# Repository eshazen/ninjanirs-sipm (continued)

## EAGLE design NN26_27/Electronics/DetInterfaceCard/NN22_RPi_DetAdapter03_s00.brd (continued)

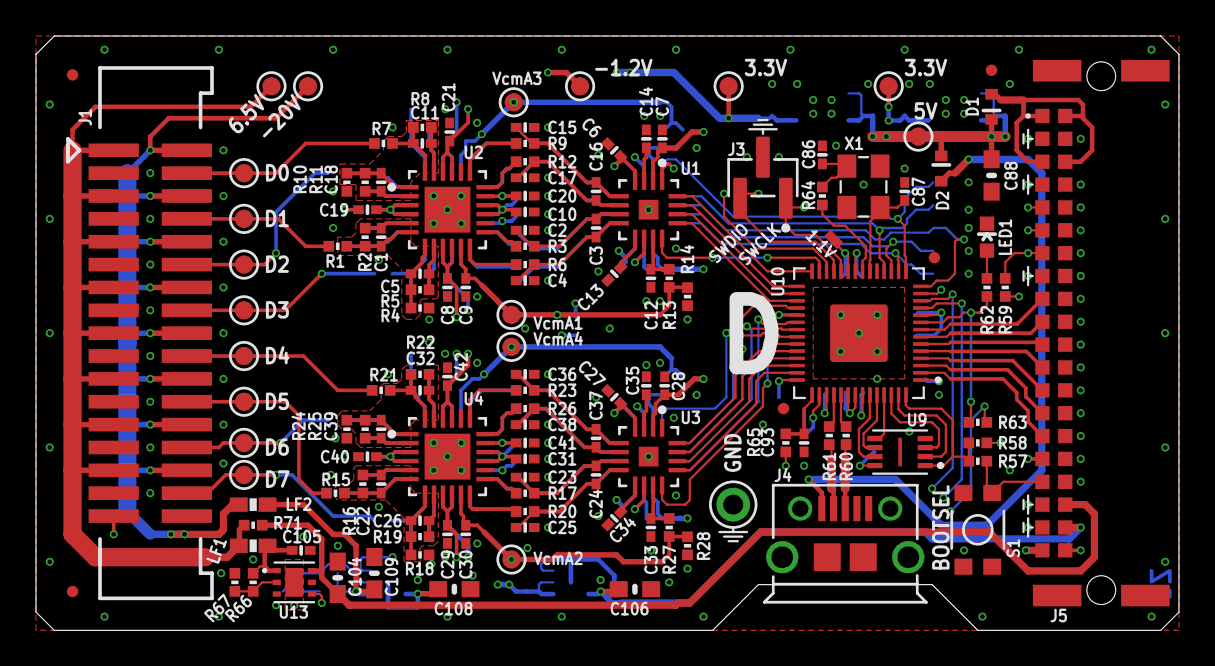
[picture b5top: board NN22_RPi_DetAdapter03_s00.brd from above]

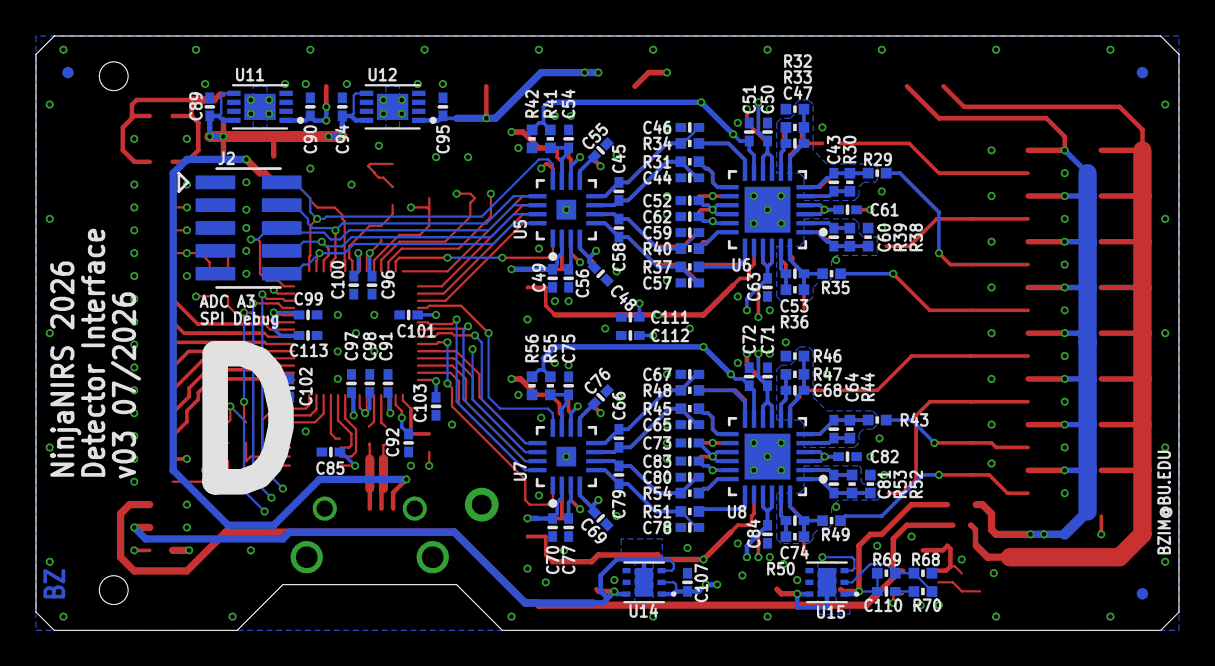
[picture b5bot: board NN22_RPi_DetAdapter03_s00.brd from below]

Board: 6 copper layers, 63.5 x 33.0 mm, 239 parts (105 on the bottom side), 156 nets.

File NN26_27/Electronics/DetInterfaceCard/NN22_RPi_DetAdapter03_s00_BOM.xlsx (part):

Designator | Value | Footprint | Populate | MPN | Manufacturer
C1 | 330p | 0402-CAP | 1 | GRM1555C1H331JA01D | Murata
C10 | 0.1u | 0402-CAP | 1 | GRM155R71H104KE14D | Murata
C100 | 0.1u | 0402-CAP | 1 | GRM155R71H104KE14D | Murata
C101 | 0.1u | 0402-CAP | 1 | GRM155R71H104KE14D | Murata
C102 | 0.1u | 0402-CAP | 1 | GRM155R71H104KE14D | Murata
C103 | 0.1u | 0402-CAP | 1 | GRM155R71H104KE14D | Murata
C104 | 10u | 0603-CAP | 1 | GRM188R6YA106MA73D | Murata
C105 | 4.7u | 0402-CAP | 1 | CL05A475MP5NRNC | Samsung
C106 | 10u | 0603-CAP | 1 | GRM188R6YA106MA73D | Murata
C107 | 4.7u | 0402-CAP | 1 | CL05A475MP5NRNC | Samsung
C108 | 10u | 0603-CAP | 1 | GRM188R6YA106MA73D | Murata
C109 | 10u | 0603-CAP | 1 | GRM188R6YA106MA73D | Murata
C11 | 330p | 0402-CAP | 1 | GRM1555C1H331JA01D | Murata
C110 | 33n | 0402-CAP | 1 | GCM155R71E333KA55D | Murata
C111 | 4.7u | 0402-CAP | 1 | CL05A475MP5NRNC | Samsung
C112 | 4.7u | 0402-CAP | 1 | CL05A475MP5NRNC | Samsung
C113 | 4.7u | 0402-CAP | 1 | CL05A475MP5NRNC | Samsung
C12 | 1u | 0402-CAP | 1 | CL05A105KP5NNNC | Samsung
C13 | 0.1u | 0402-CAP | 1 | GRM155R71H104KE14D | Murata
C14 | 1u | 0402-CAP | 1 | CL05A105KP5NNNC | Samsung
C15 | 1n | 0402-CAP | 1 | GRM1555C1H102JA01D | Murata
C16 | 1n | 0402-CAP | 1 | GRM1555C1H102JA01D | Murata
C17 | 1n | 0402-CAP | 1 | GRM1555C1H102JA01D | Murata
C18 | 330p | 0402-CAP | 1 | GRM1555C1H331JA01D | Murata
C19 | 0.1u | 0402-CAP | 1 | GRM155R71H104KE14D | Murata
C2 | 1n | 0402-CAP | 1 | GRM1555C1H102JA01D | Murata
C20 | 0.1u | 0402-CAP | 1 | GRM155R71H104KE14D | Murata
C21 | 0.1u | 0402-CAP | 1 | GRM155R71H104KE14D | Murata
C22 | 330p | 0402-CAP | 1 | GRM1555C1H331JA01D | Murata
C23 | 1n | 0402-CAP | 1 | GRM1555C1H102JA01D | Murata
C24 | 1n | 0402-CAP | 1 | GRM1555C1H102JA01D | Murata
C25 | 1n | 0402-CAP | 1 | GRM1555C1H102JA01D | Murata
C26 | 330p | 0402-CAP | 1 | GRM1555C1H331JA01D | Murata
C27 | 1u | 0402-CAP | 1 | CL05A105KP5NNNC | Samsung
C28 | 1u | 0402-CAP | 1 | CL05A105KP5NNNC | Samsung
C29 | 0.1u | 0402-CAP | 1 | GRM155R71H104KE14D | Murata
C3 | 1n | 0402-CAP | 1 | GRM1555C1H102JA01D | Murata
C30 | 0.1u | 0402-CAP | 1 | GRM155R71H104KE14D | Murata
C31 | 0.1u | 0402-CAP | 1 | GRM155R71H104KE14D | Murata
C32 | 330p | 0402-CAP | 1 | GRM1555C1H331JA01D | Murata
C33 | 1u | 0402-CAP | 1 | CL05A105KP5NNNC | Samsung
C34 | 0.1u | 0402-CAP | 1 | GRM155R71H104KE14D | Murata
C35 | 1u | 0402-CAP | 1 | CL05A105KP5NNNC | Samsung
C36 | 1n | 0402-CAP | 1 | GRM1555C1H102JA01D | Murata
C37 | 1n | 0402-CAP | 1 | GRM1555C1H102JA01D | Murata
C38 | 1n | 0402-CAP | 1 | GRM1555C1H102JA01D | Murata
C39 | 330p | 0402-CAP | 1 | GRM1555C1H331JA01D | Murata
C4 | 1n | 0402-CAP | 1 | GRM1555C1H102JA01D | Murata
C40 | 0.1u | 0402-CAP | 1 | GRM155R71H104KE14D | Murata
C41 | 0.1u | 0402-CAP | 1 | GRM155R71H104KE14D | Murata
C42 | 0.1u | 0402-CAP | 1 | GRM155R71H104KE14D | Murata
C43 | 330p | 0402-CAP | 1 | GRM1555C1H331JA01D | Murata
C44 | 1n | 0402-CAP | 1 | GRM1555C1H102JA01D | Murata
C45 | 1n | 0402-CAP | 1 | GRM1555C1H102JA01D | Murata
C46 | 1n | 0402-CAP | 1 | GRM1555C1H102JA01D | Murata
C47 | 330p | 0402-CAP | 1 | GRM1555C1H331JA01D | Murata
C48 | 1u | 0402-CAP | 1 | CL05A105KP5NNNC | Samsung
C49 | 1u | 0402-CAP | 1 | CL05A105KP5NNNC | Samsung
C5 | 330p | 0402-CAP | 1 | GRM1555C1H331JA01D | Murata
C50 | 0.1u | 0402-CAP | 1 | GRM155R71H104KE14D | Murata
C51 | 0.1u | 0402-CAP | 1 | GRM155R71H104KE14D | Murata
C52 | 0.1u | 0402-CAP | 1 | GRM155R71H104KE14D | Murata
C53 | 330p | 0402-CAP | 1 | GRM1555C1H331JA01D | Murata
C54 | 1u | 0402-CAP | 1 | CL05A105KP5NNNC | Samsung
C55 | 0.1u | 0402-CAP | 1 | GRM155R71H104KE14D | Murata
C56 | 1u | 0402-CAP | 1 | CL05A105KP5NNNC | Samsung
C57 | 1n | 0402-CAP | 1 | GRM1555C1H102JA01D | Murata
C58 | 1n | 0402-CAP | 1 | GRM1555C1H102JA01D | Murata
C59 | 1n | 0402-CAP | 1 | GRM1555C1H102JA01D | Murata
C6 | 1u | 0402-CAP | 1 | CL05A105KP5NNNC | Samsung
C60 | 330p | 0402-CAP | 1 | GRM1555C1H331JA01D | Murata
C61 | 0.1u | 0402-CAP | 1 | GRM155R71H104KE14D | Murata
C62 | 0.1u | 0402-CAP | 1 | GRM155R71H104KE14D | Murata
C63 | 0.1u | 0402-CAP | 1 | GRM155R71H104KE14D | Murata
C64 | 330p | 0402-CAP | 1 | GRM1555C1H331JA01D | Murata
C65 | 1n | 0402-CAP | 1 | GRM1555C1H102JA01D | Murata
C66 | 1n | 0402-CAP | 1 | GRM1555C1H102JA01D | Murata
C67 | 1n | 0402-CAP | 1 | GRM1555C1H102JA01D | Murata
C68 | 330p | 0402-CAP | 1 | GRM1555C1H331JA01D | Murata
C69 | 1u | 0402-CAP | 1 | CL05A105KP5NNNC | Samsung
C7 | 1u | 0402-CAP | 1 | CL05A105KP5NNNC | Samsung
C70 | 1u | 0402-CAP | 1 | CL05A105KP5NNNC | Samsung
C71 | 0.1u | 0402-CAP | 1 | GRM155R71H104KE14D | Murata
C72 | 0.1u | 0402-CAP | 1 | GRM155R71H104KE14D | Murata
C73 | 0.1u | 0402-CAP | 1 | GRM155R71H104KE14D | Murata
C74 | 330p | 0402-CAP | 1 | GRM1555C1H331JA01D | Murata
C75 | 1u | 0402-CAP | 1 | CL05A105KP5NNNC | Samsung
C76 | 0.1u | 0402-CAP | 1 | GRM155R71H104KE14D | Murata
C77 | 1u | 0402-CAP | 1 | CL05A105KP5NNNC | Samsung
C78 | 1n | 0402-CAP | 1 | GRM1555C1H102JA01D | Murata
C79 | 1n | 0402-CAP | 1 | GRM1555C1H102JA01D | Murata
C8 | 0.1u | 0402-CAP | 1 | GRM155R71H104KE14D | Murata
C80 | 1n | 0402-CAP | 1 | GRM1555C1H102JA01D | Murata
C81 | 330p | 0402-CAP | 1 | GRM1555C1H331JA01D | Murata
C82 | 0.1u | 0402-CAP | 1 | GRM155R71H104KE14D | Murata
C83 | 0.1u | 0402-CAP | 1 | GRM155R71H104KE14D | Murata
C84 | 0.1u | 0402-CAP | 1 | GRM155R71H104KE14D | Murata
C85 | 0.1u | 0402-CAP | 1 | GRM155R71H104KE14D | Murata
C86 | 27p | 0402-CAP | 1 | GCM1555C1H270JA16D | Murata
C87 | 27p | 0402-CAP | 1 | GCM1555C1H270JA16D | Murata
C88 | 10u | 0603-CAP | 1 | GRM188R6YA106MA73D | Murata
C89 | 4.7u | 0402-CAP | 1 | CL05A475MP5NRNC | Samsung
C9 | 0.1u | 0402-CAP | 1 | GRM155R71H104KE14D | Murata
C90 | 4.7u | 0402-CAP | 1 | CL05A475MP5NRNC | Samsung
C91 | 4.7u | 0402-CAP | 1 | CL05A475MP5NRNC | Samsung
C92 | 4.7u | 0402-CAP | 1 | CL05A475MP5NRNC | Samsung
C93 | 4.7u | 0402-CAP | 1 | CL05A475MP5NRNC | Samsung
C94 | 4.7u | 0402-CAP | 1 | CL05A475MP5NRNC | Samsung
C95 | 4.7u | 0402-CAP | 1 | CL05A475MP5NRNC | Samsung
C96 | 0.1u | 0402-CAP | 1 | GRM155R71H104KE14D | Murata
C97 | 0.1u | 0402-CAP | 1 | GRM155R71H104KE14D | Murata
C98 | 0.1u | 0402-CAP | 1 | GRM155R71H104KE14D | Murata
C99 | 0.1u | 0402-CAP | 1 | GRM155R71H104KE14D | Murata
D1 | SBR1A20T5 | SOD523 | 1 | SBR1A20T5-7 | Diodes Inc.
D2 | SBR1A20T5 | SOD523 | 1 | SBR1A20T5-7 | Diodes Inc.
FID1 | FIDUCIALUFIDUCIAL | MICRO-FIDUCIAL | 0
FID2 | FIDUCIALUFIDUCIAL | MICRO-FIDUCIAL | 0
FID3 | FIDUCIALUFIDUCIAL | MICRO-FIDUCIAL | 0
FID4 | FIDUCIALUFIDUCIAL | MICRO-FIDUCIAL | 0
FID5 | FIDUCIALUFIDUCIAL | MICRO-FIDUCIAL | 0
FID6 | FIDUCIALUFIDUCIAL | MICRO-FIDUCIAL | 0
FID7 | FIDUCIALUFIDUCIAL | MICRO-FIDUCIAL | 0
FID8 | FIDUCIALUFIDUCIAL | MICRO-FIDUCIAL | 0
J1 | M17X2 | M17X2_0.050_SHF | 1 | SHF-117-01-L-D-SM | Samtec
J2 | M05X2_SMD_0.050_NOCREAM | M05X2_0.050_SMD_NO_CREAM | 0
J3 | M03X1_0.050_SMD_NO_CREAM | M03X1_0.050_SMD_NO_CREAM | 0
J4 | USB-MICRO | USB-MICRO | 1 | 10118194-0001LF | Amphenol Communications Solutions
J5 | M20X2_HARFLEX_M | M20X2_HARFLEX_M | 1 | 15150402601000 | HARTING Elektronik
LED1 |  | LED-0603 | 1 | LTST-C191KRKT | Lite-On
LF1 | FERRITE0603 | 0603-FER | 1 | BLM18AG601SN1D | Murata
LF2 | FERRITE0603 | 0603-FER | 1 | BLM18AG601SN1D | Murata
R1 | 18k | 0402-RES | 1 | RR0510P-183-D | Susumu
R10 | 18k | 0402-RES | 1 | RR0510P-183-D | Susumu
R11 | 2.2k | 0402-RES | 1 | RR0510P-222-D | Susumu
R12 | 33 | 0402-RES | 1 | CRCW040233R0FKEDC | Vishay
R13 | 18k | 0402-RES | 1 | RR0510P-183-D | Susumu
R14 | 18k | 0402-RES | 1 | RR0510P-183-D | Susumu
R15 | 18k | 0402-RES | 1 | RR0510P-183-D | Susumu
R16 | 2.2k | 0402-RES | 1 | RR0510P-222-D | Susumu
R17 | 33 | 0402-RES | 1 | CRCW040233R0FKEDC | Vishay
R18 | 18k | 0402-RES | 1 | RR0510P-183-D | Susumu
R19 | 2.2k | 0402-RES | 1 | RR0510P-222-D | Susumu
R2 | 2.2k | 0402-RES | 1 | RR0510P-222-D | Susumu
R20 | 33 | 0402-RES | 1 | CRCW040233R0FKEDC | Vishay
R21 | 18k | 0402-RES | 1 | RR0510P-183-D | Susumu
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
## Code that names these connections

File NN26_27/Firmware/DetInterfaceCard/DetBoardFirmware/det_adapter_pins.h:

// ---  NinjaNIRS 2022  ---
// Pin constants for NN22_RPi_DetAdapter00_s02_R66R67 board
//
// Initial version: 2022-12-12
// Bernhard Zimmermann - bzim@bu.edu
// Boston University Neurophotonics Center
//


// Backplane pins: GPIO00 - GPIO06
const uint UART_TX_PIN = 0;
const uint UART_RX_PIN = 1;
const uint BOARD_SELECT_PIN = 2;
//const uint TRG_PIN = 3; // check also adcacq.pio
const uint END_CYC_PIN = 4;
const uint STATUS_SELECT_PIN = 5;
const uint RESERVED_PIN = 6;

// Misc Pins
const uint A_COMM_PIN = 7;
const uint OPT_EN_VP_PIN = 8;
const uint OPT_EN_VN_PIN = 9;
const uint LED_R_PIN = 10;
const uint LED_G_PIN = 11;

// ADC pins
// 4 ADCs with dual-data SPI interface
const uint CSN_A3_PIN = 12;
const uint SCLK_A3_PIN = 13;
const uint MOSI_A3_PIN = 14;
const uint MISO_A3_PIN = 15;
 
const uint CSN_A1_PIN = 16;
const uint SCLK_A1_PIN = 17;
const uint MOSI_A1_PIN = 18;
//const uint MISOB_A1_PIN = 19; // only using one MISO wire
const uint MISO_A1_PIN = 20;

const uint CSN_A4_PIN = 21;
const uint SCLK_A4_PIN = 22;
const uint MOSI_A4_PIN = 23;
const uint MISO_A4_PIN = 24;

const uint CSN_A2_PIN = 25;
const uint SCLK_A2_PIN = 26;
const uint MOSI_A2_PIN = 27;
//const uint MISOB_A2_PIN = 28; // only using one MISO wire
const uint MISO_A2_PIN = 29;

// Map adc results to detectors
const uint DET_ADC_MAP[] = {0, 1, 5, 4, 2, 3, 7, 6};

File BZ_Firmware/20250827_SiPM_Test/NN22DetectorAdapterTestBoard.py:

# ---  NinjaNIRS 2022  ---
# Helper module for NN22_RPi_DetAdapter00_TestBoard00
#
# Initial version: 2022-12-19
# Bernhard Zimmermann - bzim@bu.edu
# Boston University Neurophotonics Center
#

import board
import digitalio
import time
import pwmio
import busio
from analogio import AnalogIn

class TestBoard:
    def __init__(self):
        # Init GPIO
        self.ledR = digitalio.DigitalInOut(board.GP13)
        self.ledG = digitalio.DigitalInOut(board.GP14)
        self.ledR.direction = digitalio.Direction.OUTPUT
        self.ledG.direction = digitalio.Direction.OUTPUT

        self.targetRun = digitalio.DigitalInOut(board.GP12) # on target: RP2040 'run' pin
        self.targetBoardSelect = digitalio.DigitalInOut(board.GP7) # on target: GPIO02
        self.targetTrig = digitalio.DigitalInOut(board.GP8) # on target: GPIO03
        self.targetEndCyc = digitalio.DigitalInOut(board.GP9) # on target: GPIO04
        self.targetStatusSelect = digitalio.DigitalInOut(board.GP10) # on target: GPIO05
        #targetReservedPin = board.GP11 # on target: GPIO06

        self.targetRun.direction = digitalio.Direction.OUTPUT
        self.targetBoardSelect.direction = digitalio.Direction.OUTPUT
        self.targetBoardSelect.value = 1
        self.targetTrig.direction = digitalio.Direction.OUTPUT
        self.targetEndCyc.direction = digitalio.Direction.OUTPUT
        self.targetStatusSelect.direction = digitalio.Direction.OUTPUT

        self.buzz = pwmio.PWMOut(board.GP22, duty_cycle=0, frequency=1000, variable_frequency=True)
        #self.buzz.duty_cycle = 2**15
        self.button = digitalio.DigitalInOut(board.GP15)

        self.dac = Bh2226f()
        self.dac.setCHvalR0(0,0)

        self.nSamples = 10
        self.adcCalConst = -6.25e-4/self.nSamples # convert ADC value to voltage

        self.uart = busio.UART(board.GP4, board.GP5, baudrate=6000000)

        self.analogVN20 = AnalogIn(board.A0)
        self.analogV6P5 = AnalogIn(board.A1)
        self.analogV3P3 = AnalogIn(board.A2)

        self.resetTargetBoard()

    def getSupplyRails(self):
        # This function reads the voltages of three supply rails on
        # the target detector adapter card.
        reslist = []
        val = self.analogV6P5.value * 3.3 / 65535 # voltage at the RP2040 pin
        val = val * (3.3+5.6)/3.3 # voltage at rail, considering voltage divider
        reslist.append(val)
        val = self.analogV3P3.value * 3.3 / 65535 # voltage at the RP2040 pin
        val = val * (3.3+3.3)/3.3 # voltage at rail, considering voltage divider
        reslist.append(val)
        val = self.analogVN20.value * 3.3 / 65535 # voltage at the RP2040 pin
        val = val - 33/3.3*(3.3-val) # voltage at rail, considering voltage divider
        reslist.append(val)
        return reslist

    def getOneTargetSample(self):
        # This function collects one sample of all 8 ADC channels of the
        # connected target detector adapter card.
        self.uart.reset_input_buffer()
        for isample in range(0,self.nSamples+1): # first sample will be discarded by target
            self.targetTrig.value = 1
            self.targetTrig.value = 0
        self.targetEndCyc.value = 1
        self.targetEndCyc.value = 0

        self.targetBoardSelect.value = 0
        buf = self.uart.read(28)
        self.targetBoardSelect.value = 1

        if buf is None:
            print("No data received from target.")
            return []
        elif len(buf)<28:
            print("Not enough data received from target.")
            return []

        # check packet header bytes
        if not(buf[0]==253 and buf[1]==252):
            print("Bad header received from target.")

        # check sample counter
        if buf[2]!=self.sampleCount:
            print("Bad sample count received from target.")
        self.sampleCount = (buf[2]+1)%256

        # convert received payload bytes to results list
        # N_BYTES_PER_DET = 3
        reslist = []
        for ich in range(0, 8):
            val = buf[3+ich*3] + buf[3+ich*3+1]*256 + buf[3+ich*3+2]*65536
            # correct for two's complement and invert result
            if val>8388607: # equivalent: val>((2**23)-1)
                val = 16777216-val # equivalent: 2**24-val
            else:
                val = -val
            reslist.append(val)

        # check packet trailer byte
        if buf[27]!=0:
            print("Bad trailer received from target.")

        return reslist

    def getTargetStatus(self):
        # This fuction collects one status packet of the
        # connected target detector adapter card.
        self.uart.reset_input_buffer()
        self.targetStatusSelect.value = 1
        self.targetEndCyc.value = 1
        self.targetEndCyc.value = 0
        self.targetStatusSelect.value = 0

        self.targetBoardSelect.value = 0
        buf = self.uart.read(18)
        self.targetBoardSelect.value = 1

        if buf is None:
            print("No data received from target.")
            return []
        elif len(buf)<18:
            print("Not enough data received from target.")
            return []

        # check packet header bytes
        if not(buf[0]==239 and buf[1]==238):
            print("Bad status packet header received from target.")

        # check sample counter
        if buf[2]!=self.sampleCount:
            print("Bad sample count received from target.")
        self.sampleCount = (buf[2]+1)%256

        # convert received payload bytes to results list
        reslist = []
        #reslist.append(buf[3:11].hex()) # unique ID # does not work in this Python version
        reslist.append(''.join('{1:02x}'.format(*d) for d in enumerate(buf[3:11])))
        reslist.append('v{:d}.{:d}'.format(buf[11], buf[12])) # firmware version
        temp = 27.0 - ((buf[13] + buf[14]*(1<<8)) * 3.3/(1<<12) - 0.706)/0.001721
        reslist.append('{:4.1f}C'.format(temp))

        # check packet trailer byte
        if buf[17]!=0:
            print("Bad status packet trailer received from target.")

        return reslist

    def resetTargetBoard(self):
        self.targetRun.value = 0
        time.sleep(0.01)
        self.targetRun.value = 1
        time.sleep(1.5)
        self.sampleCount = 0

class Bh2226f:
    # class for ROHM BH2226F 8 bit 8 channel D/A Converter
    # only functionality required for this project implemented
    def __init__(self):
        # set on-board Vreg to PWM mode to reduce ripple
        self.pwmmode = digitalio.DigitalInOut(board.GP23)
        self.pwmmode.direction = digitalio.Direction.OUTPUT
        self.pwmmode.value = True

        # pin definitions for serial interface
        self.resetn = digitalio.DigitalInOut(board.GP20)
        self.resetn.direction = digitalio.Direction.OUTPUT
        self.resetn.value = False
        self.clk = digitalio.DigitalInOut(board.GP18)
        self.clk.direction = digitalio.Direction.OUTPUT
        self.clk.value = False
        self.csn = digitalio.DigitalInOut(board.GP17)
        self.csn.direction = digitalio.Direction.OUTPUT
        self.csn.value = True
        self.so = digitalio.DigitalInOut(board.GP16) # "MISO"
        self.di = digitalio.DigitalInOut(board.GP19) # "MOSI"
        self.di.direction = digitalio.Direction.OUTPUT
        self.di.value = False

        # start up DAC
        self.resetn.value = True # release reset
        time.sleep(0.001)
        self.powerDownRelease()
        self.selectDA() # set outputs to analog mode

    def sendInstruction(self, addr, val): # send a single instruction
        data = (addr<<8) + val
        self.csn.value = False
        for ibit in range(11, -1, -1):
            self.di.value = (data >> ibit) &1
            self.clk.value = False
            self.clk.value = True
        self.csn.value = True
        self.clk.value = False
        self.di.value = False

    def setCHval(self, ch, val): # ch in range [0..7], val in range [0..255]
        addrlist = [0b1000, 0b0100, 0b1100, 0b0010, 0b1010, 0b0110, 0b1110, 0b0001]
        self.sendInstruction(addrlist[ch], val)

    def setCHvalR0(self, ch, val): # set all others to 0
        for nch in range(0, 8):
            if nch == ch:
                nval = val
            else:
                nval = 0
            self.setCHval(nch, nval)

    def powerDownRelease(self): # init command required by dac
        self.sendInstruction(0b1001, 0)

    def selectDA(self): # set all outputs to analog mode
        self.sendInstruction(0b0011, 0b11111111)

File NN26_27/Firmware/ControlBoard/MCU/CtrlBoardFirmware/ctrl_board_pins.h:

// ---  NinjaNIRS 2022  ---
// Pin constants for ControlBoard02_v01 board
// This is the new control board with LCMXO2-7000HC FPGA.
//
// Initial version: 2024-04-19
// Bernhard Zimmermann - bzim@bu.edu
// Boston University Neurophotonics Center
//

// FPGA interface pins
const uint UART_TX_PIN = 12;
const uint UART_RX_PIN = 13;
const uint BOARD_SELECT_PIN = 14;  //CTS flow control
const uint END_CYC_PIN = 15;
const uint STATUS_SELECT_PIN = 16;
const uint RUN_IND_PIN = 17; // Run indicator input
const uint UART1_TX_PIN = 20;
const uint UART1_RX_PIN = 21;

// Qwiic RPiP port for IMU
const uint I2C_SDA_PIN = 10;
const uint I2C_SCL_PIN = 11;
#define ACC_I2C i2c1

// Misc Pins
const uint LED_R_PIN = 5;
const uint LED_G_PINS[] = {4, 3};
const uint BUTTON_PIN = 6;
const uint BUZZER_PIN = 7;
const uint FAN_PWR_PIN = 24;
const uint FAN_SENSE_PIN = 25;
const uint V12_CURR_SENSE_PIN = 26;
const uint V12_CURR_SENSE_ACH = 0;
const uint AUXIO_PINS[] = {29, 27};
const uint AUXIO_ACHS[] = {3, 1};
const uint VIN_SENSE_PIN = 28;
const uint VIN_SENSE_ACH = 2;
const uint TEMP_ACH = 4; // Internal temperature sensor virtual pin

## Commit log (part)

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2025-05-07 starting on bias voltage trim circuit
2025-05-08 working on sch
2025-05-08 working on layout
2025-05-09 new placement
2025-05-09 candidate V1.0 LT3014 board
2025-05-11 ordering
2025-05-12 small tweaks before V1.0 fab
2025-06-04 readme
2025-06-04 readme, schematic notes
2025-06-11 testing notes
2025-06-26 starting schem for HV/splitter for SiPM
2025-06-30 working on SiPM power supply schem
2025-06-30 starting placement
2025-06-30 random placement for area estimate
2025-06-30 add ISP
2025-06-30 fix some MCU pins
2025-07-01 working on 2.5 in placement
2025-07-01 routing madness
2025-07-02 working on bias filter changes
2025-07-02 routing
2025-07-03 routing almost done
2025-07-03 routing complete
2025-07-03 draft schematic PDF and Gerbers
2025-07-03 working on BOM
2025-07-03 finish BOM entries on schematic
2025-07-07 working on layout updates
2025-07-07 Candidate V1.0 for review/fab
2025-07-07 update PDF schematic
2025-07-08 Update gerber zip
2025-07-09 add mtg holes, L2 gnd fill
2025-07-10 finished V1.0 hv/splitter?
2025-07-23 testing
2025-07-23 testing digi pot
2025-07-29 digital pot working, updated ECOs
2025-08-04 software fixes, update README
2025-08-27 add temperature readout
2025-09-03 update software, add dark box
2025-09-10 dark box for testing
2025-09-10 tweak box
2025-09-11 docs and scripts
2025-09-12 new operating firmware, some doco
2026-02-03 update testing
2026-02-03 working on xtalk tests
2026-02-05 fix typo
2026-02-10 more testing
2026-02-26 More tests
2026-03-03 Update README and tweak voltage / ADC numbers
